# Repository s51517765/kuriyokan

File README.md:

# Kuriyokan

## 概要 (Overview)

クレジットカードサイズのキーボード

## 実物イメージ (Image)

## 技術的解説 (Technical explanation)

## 部品リスト（Parts list）

| 部品               | 種類           | 数量 |
| ------------------ | -------------- | ---- |
| PCB                | -              | 1    |
| マイコン           | Pro Mocro      | 1    |
| ピンヘッダ         | 12pin          | 2    |
| キーボードスイッチ | Cherry MX 互換 | 6    |
| キーキャップ       | Cherry MX 互換 | 6    |
| タクトスイッチ     | 6mm 角         | 3    |
| ダイオード         | 1N4148         | 8    |

## ライセンス (License)

This software is released under the MIT License, see LICENSE.

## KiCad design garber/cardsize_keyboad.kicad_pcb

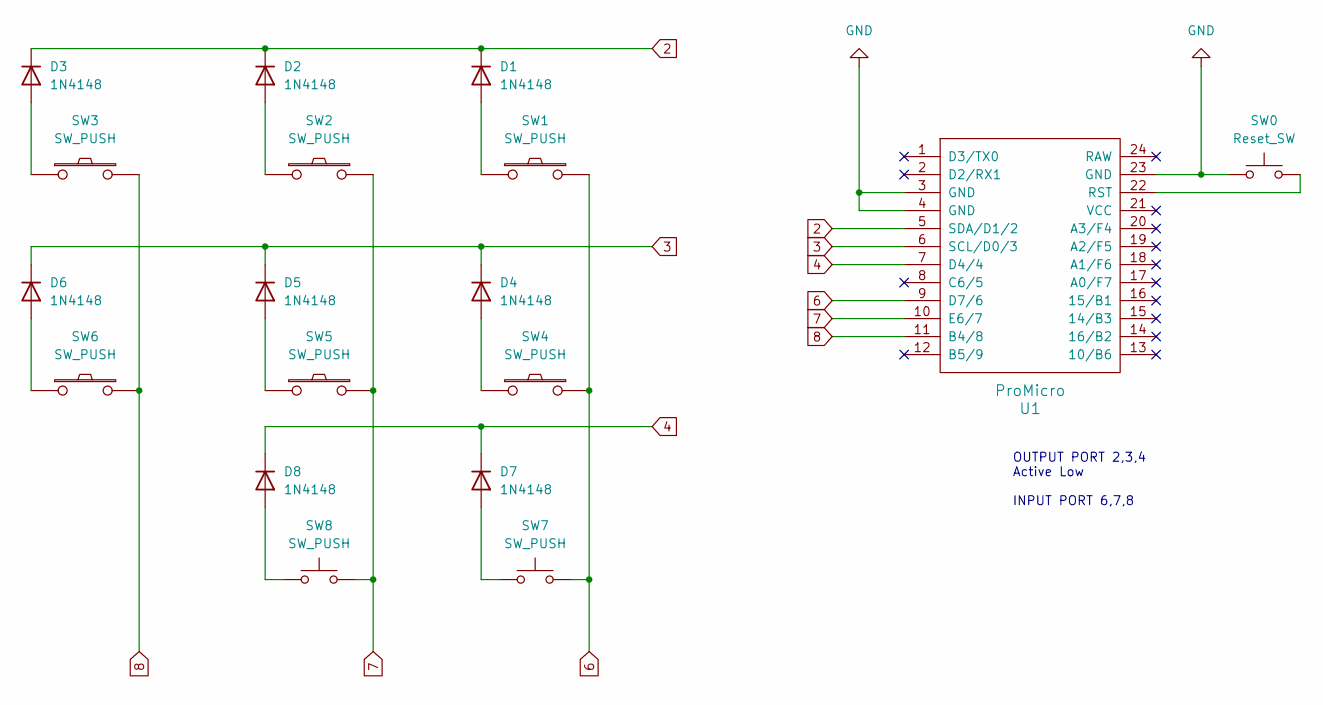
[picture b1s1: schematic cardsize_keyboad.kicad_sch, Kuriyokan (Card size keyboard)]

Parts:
D1, D2, D3, D4, D5, D6, D7, D8: 1N4148; D_DO-35_SOD27_P7.62mm_Horizontal
SW0: Reset_SW; SW_TH_Tactile_Omron_B3F-10xx
SW1, SW2, SW3, SW4, SW5, SW6: SW_PUSH; SW_Cherry_MX_1.00u_Plate
SW7, SW8: SW_PUSH; SW_TH_Tactile_Omron_B3F-10xx
U1: ProMicro; ProMicro_v3

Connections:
6: SW1.2, SW4.2, SW7.2, U1.9 (D7/6)
7: SW2.2, SW5.2, SW8.2, U1.10 (E6/7)
8: SW3.2, SW6.2, U1.11 (B4/8)
GND: SW0.1, U1.3 (GND), U1.4 (GND), U1.23 (GND)
unnamed: D1.2 (A), SW1.1
unnamed: D1.1 (K), D2.1 (K), D3.1 (K), U1.5 (SDA/D1/2)
unnamed: D2.2 (A), SW2.1
unnamed: D3.2 (A), SW3.1
unnamed: D4.2 (A), SW4.1
unnamed: D4.1 (K), D5.1 (K), D6.1 (K), U1.6 (SCL/D0/3)
unnamed: D5.2 (A), SW5.1
unnamed: D6.2 (A), SW6.1
unnamed: D7.2 (A), SW7.1
unnamed: D7.1 (K), D8.1 (K), U1.7 (D4/4)
unnamed: D8.2 (A), SW8.1
unnamed: SW0.2, U1.22 (RST)

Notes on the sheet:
OUTPUT PORT 2,3,4 Active Low INPUT PORT 6,7,8

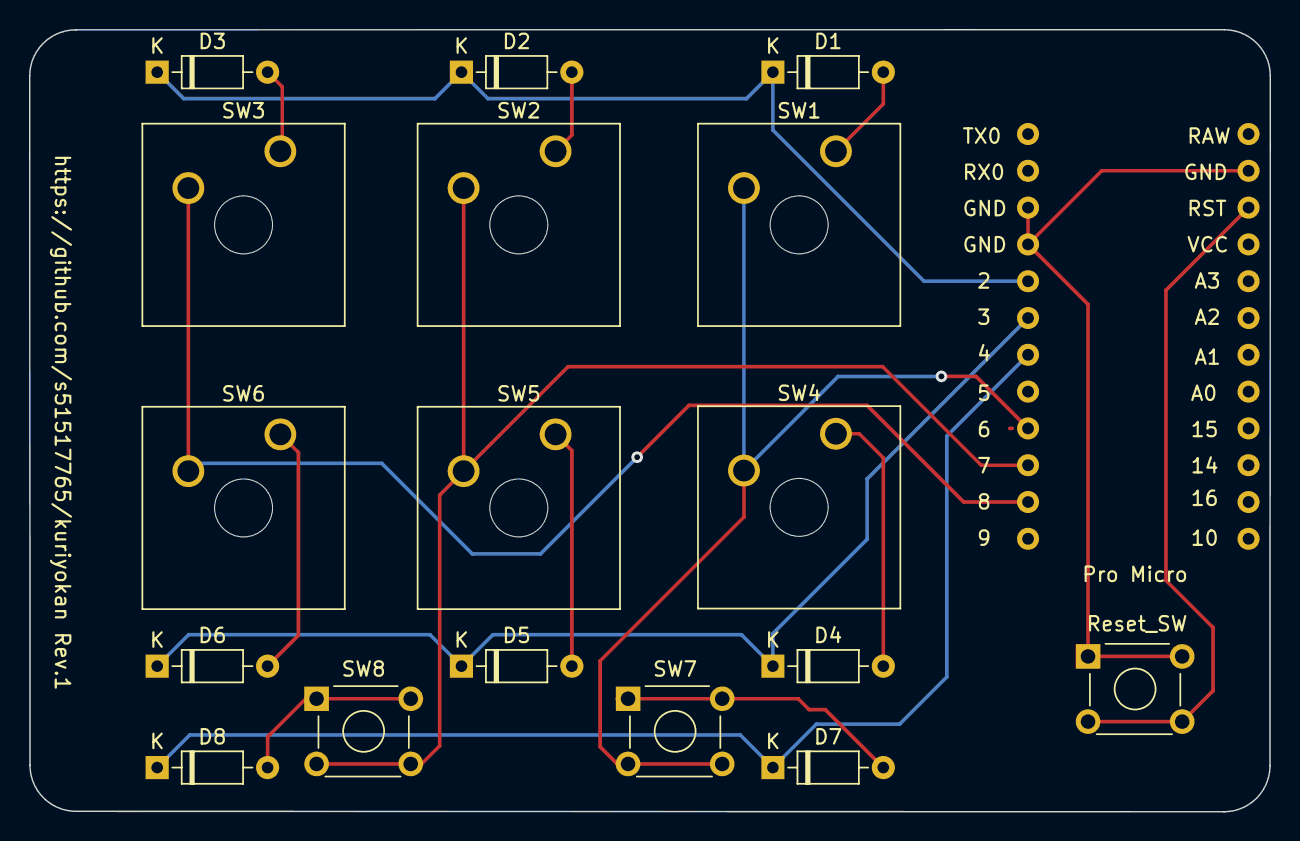
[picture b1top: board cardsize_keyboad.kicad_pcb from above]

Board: 2 copper layers, 85.6 x 54.0 mm, 18 parts (1 on the bottom side), 16 nets.

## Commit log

2024-01-20 Create LICENSE
2024-01-20 Add Readme
2024-02-04 FW first commit
2024-05-01 文字列対応、リファクタリング
2025-10-25 ホイールスクロール機能追加
2025-10-25 キーマップページ追加
2026-02-18 ホイルスクロールを追加
